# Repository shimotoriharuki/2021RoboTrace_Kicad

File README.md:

# 2021RoboTrace_Kicad

This repository contains circuit data for line-following robot ([UnderBird](https://www.youtube.com/watch?v=3UgktZoH9lk)).

Sourse code is [HERE](https://github.com/shimotoriharuki/2021RoboTracer).

Electronic components list is [HERE](https://lizard-building-630.notion.site/Electronic-components-list-d9b10301a8f747e9818a21101504a1fe).

# License: [GNU General Public License v3.0](https://github.com/shimotoriharuki/2021RoboTrace_Kicad/blob/master/COPYING)

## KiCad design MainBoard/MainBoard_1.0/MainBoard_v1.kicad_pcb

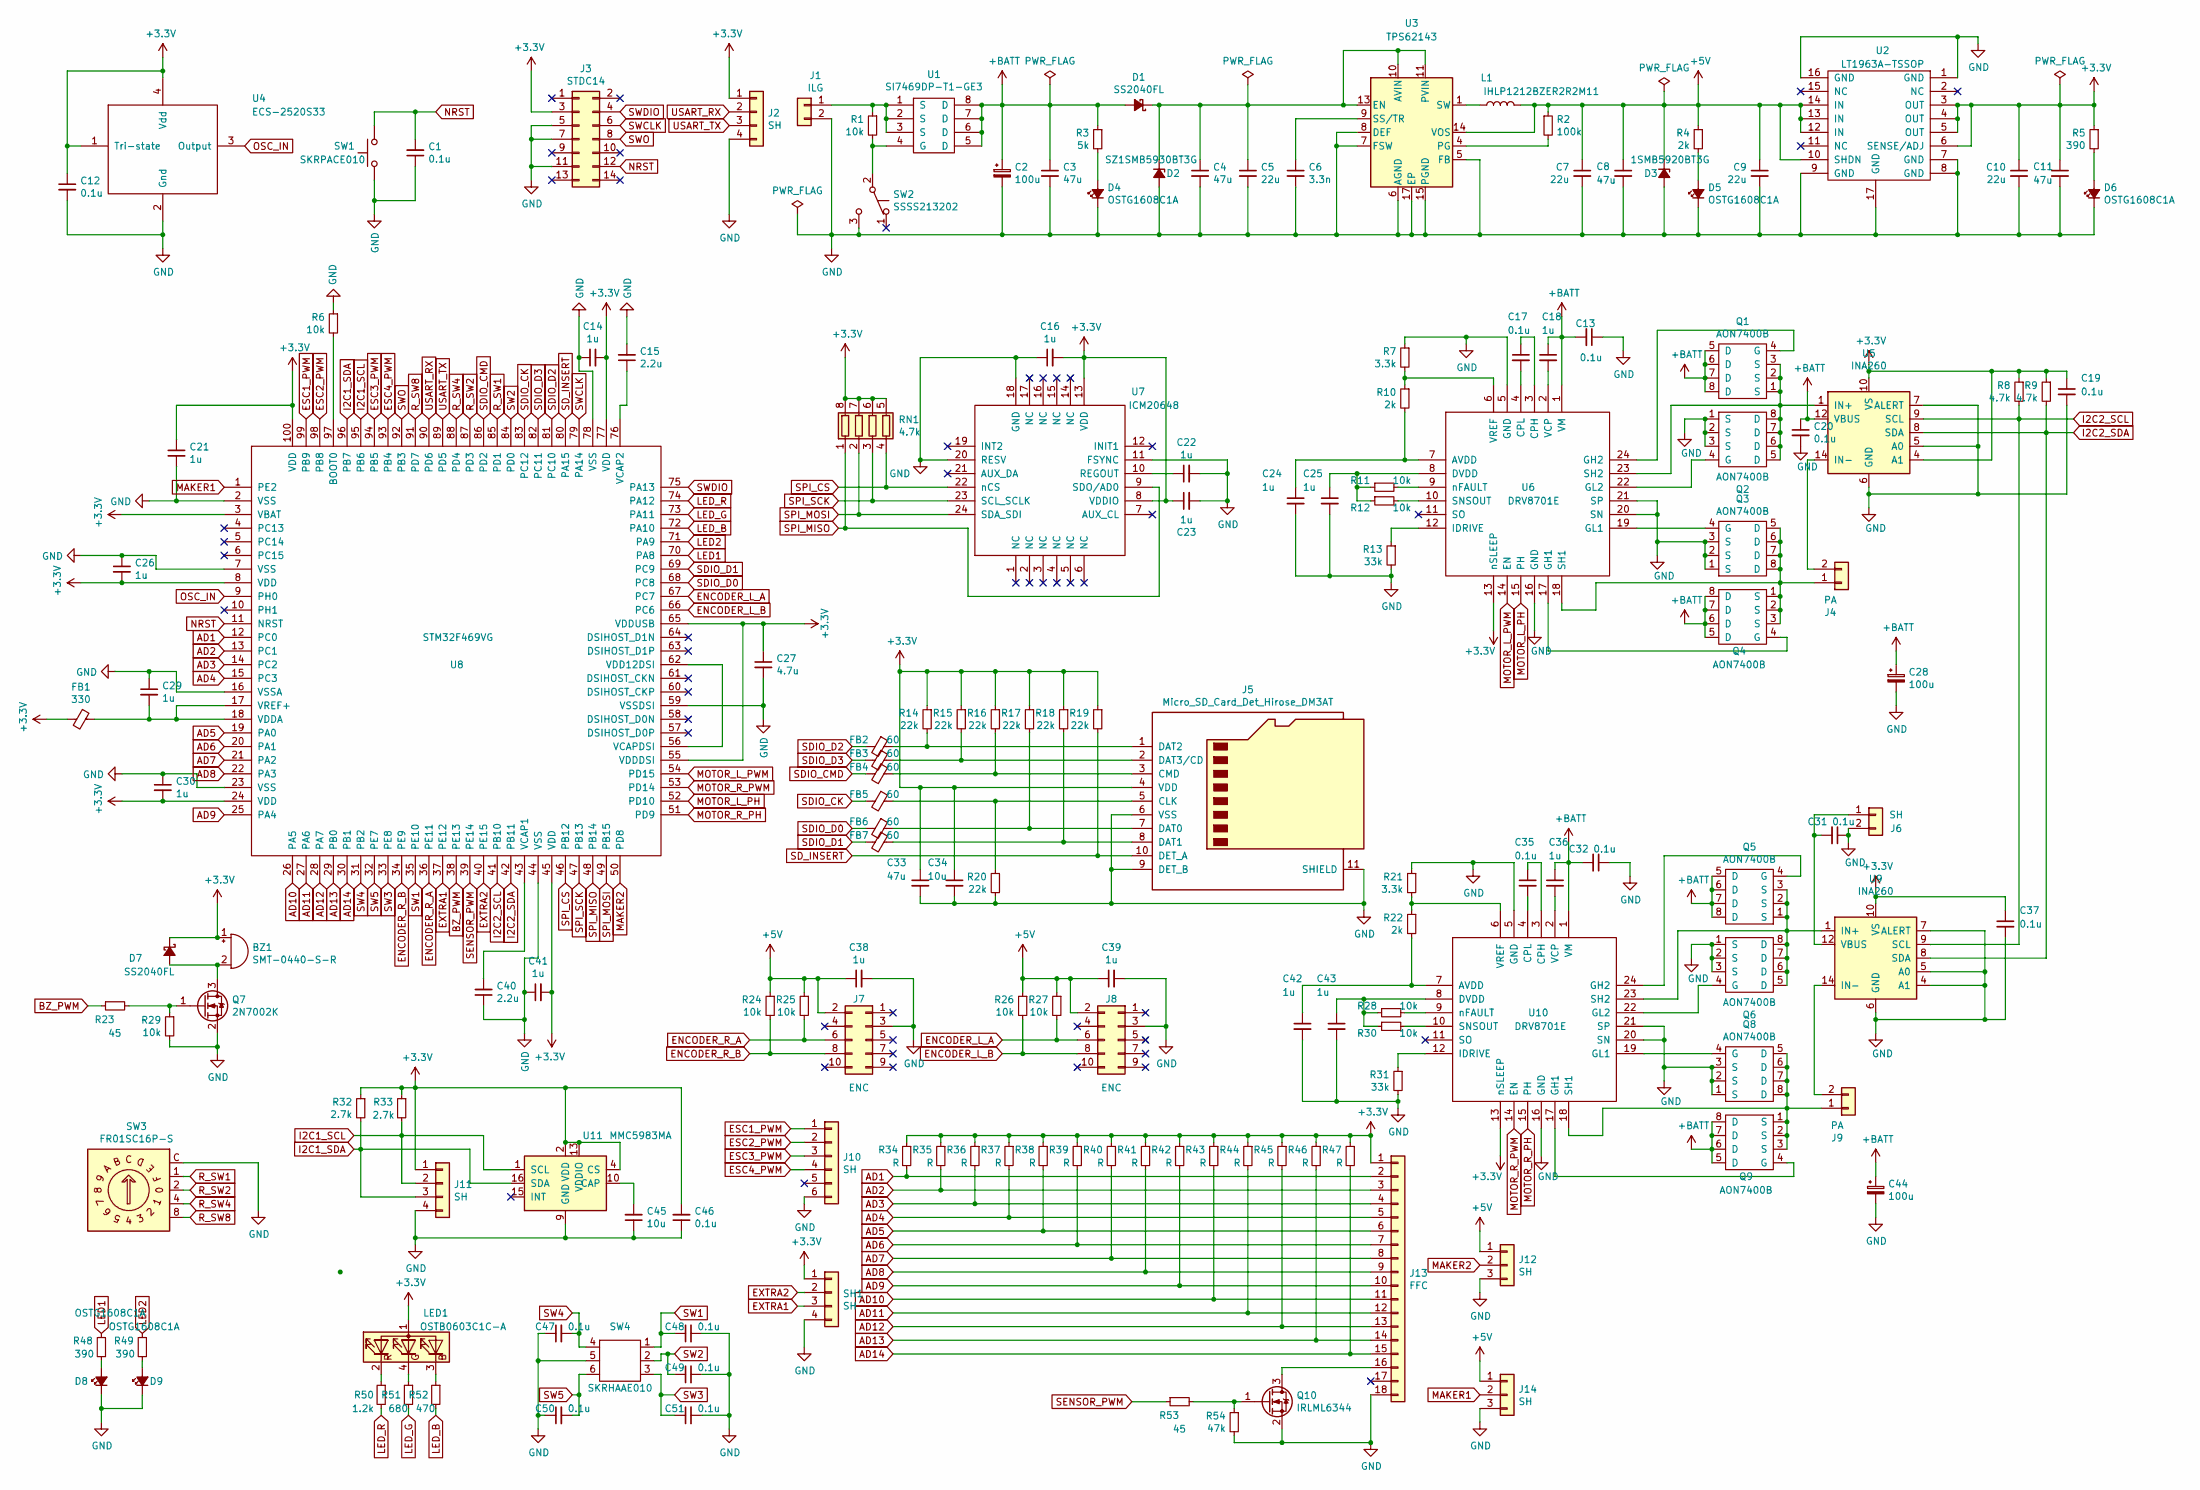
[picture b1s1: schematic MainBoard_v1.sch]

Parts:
BZ1: SMT-0440-S-R
C1, C12, C13, C17, C19, C20, C31, C32, C35, C37, C46, C47, C48, C49, C50, C51: 0.1u; C_0603
C2: 100u; CP_Elec_6.3x5.9
C3, C4, C8, C11, C33: 47u; C_1210
C5, C7, C9, C10: 22u; C_0805
C6: 3.3n; C_0603
C14, C16, C18, C21, C22, C23, C24, C25, C26, C29, C30, C36, C38, C39, C41, C42, C43: 1u; C_0603
C15, C40: 2.2u; C_0603
C27: 4.7u; C_0603
C28, C44: 100u; CP_Elec_5x5.8
C34, C45: 10u; C_0603
D1, D7: SS2040FL; D_SOD-123F
D2: SZ1SMB5930BT3G; 1SMB5930BT3G
D3: 1SMB5920BT3G; 1SMB5930BT3G
D4, D5, D6, D8, D9: OSTG1608C1A; LED_0603
FB1: 330; L_0603
FB2, FB3, FB4, FB5, FB6, FB7: 60; L_0603
J1: ILG; ILG_2pin
J2, J11: SH; JST_SH_BM04B-SRSS-TB_04x1.00mm_Straight
J3: STDC14; PinHeader_2x07_P1.27mm_Vertical_SMD
J4, J9: PA; PA_2pin
J5: Micro_SD_Card_Det_Hirose_DM3AT; Hirose_DM3AT-SF-PEJM5
J6: SH; JST_SH_BM02B-SRSS-TB_02x1.00mm_Straight
J7, J8: ENC; Pin_Header_Straight_2x05_Pitch1.27mm
J10: SH; JST_SH_BM06B-SRSS-TB_06x1.00mm_Straight
J12, J14: SH; JST_SH_BM03B-SRSS-TB_03x1.00mm_Straight
J13: FFC; Molex_FFC_18
L1: IHLP1212BZER2R2M11
LED1: OSTB0603C1C-A
Q1, Q2, Q3, Q4, Q5, Q6, Q8, Q9: AON7400B; DFN-8-1EP_3x3mm_P0.65mm_EP1.55x2.4mm
Q7: 2N7002K; SOT-23
Q10: IRLML6344; SOT-23
R1, R6, R11, R12, R24, R25, R26, R27, R28, R29, R30: 10k; R_0603
R2: 100k; R_0603
R3: 5k; R_0603
R4, R10, R22: 2k; R_0603
R5, R48, R49: 390; R_0603
R7, R21: 3.3k; R_0603
R8, R9: 4.7k; R_0603
R13, R31: 33k; R_0603
R14, R15, R16, R17, R18, R19, R20: 22k; R_0603
R23, R53: 45; R_0603
R32, R33: 2.7k; R_0603
R34, R35, R36, R37, R38, R39, R40, R41, R42, R43, R44, R45, R46, R47: R; R_0603
R50: 1.2k; R_0603
R51: 680; R_0603
R52: 470; R_0603
R54: 47k; R_0603
RN1: 4.7k; R_Array_Convex_4x1206
SH1: SH; JST_SH_BM04B-SRSS-TB_04x1.00mm_Straight
SW1: SKRPACE010
SW2: SSSS213202
SW3: FR01SC16P-S; FR01SC16P
SW4: SKRHAAE010
U1: SI7469DP-T1-GE3; SO-8_PowerPAK_Vishay_Single
U2: LT1963A-TSSOP; TSSOP-16-1EP_4.4x5mm_Pitch0.65mm
U3: TPS62143; TPS62143RGTR
U4: ECS-2520S33; Crystal_SMD_2520-4pin_2.5x2.0mm
U5, U9: INA260; TSSOP-16_4.4x5mm_Pitch0.65mm
U6, U10: DRV8701E; DRV8701ERGET
U7: ICM20648
U8: STM32F469VG; LQFP-100_14x14mm_Pitch0.5mm
U11: MMC5983MA

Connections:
+3V3: BZ1.1 (-), C10.1, C11.1, C12.1, C14.2, C16.2, C19.1, C21.1, C23.1, C26.2, C27.1, C30.2, C33.1, C34.1, C37.1, C41.2, C46.2, D7.1 (K), FB1.2, J2.1, J3.3, J5.4 (VDD), J11.1, J13.1, LED1.1, R5.1, R8.1, R9.1, R14.1, R15.1, R16.1, R17.1, R18.1, R19.1, R32.1, R33.1, R34.1, R35.1, R36.1, R37.1, R38.1, R39.1, R40.1, R41.1, R42.1, R43.1, R44.1, R45.1, R46.1, R47.1, RN1.5 (R4.2), RN1.6 (R3.2), RN1.7 (R2.2), RN1.8 (R1.2), SH1.1, U2.3 (OUT), U2.4 (OUT), U2.5 (OUT), U2.6 (SENSE/ADJ), U4.1 (Tri-state), U4.4 (Vdd), U5.4 (A1), U5.10 (VS), U6.13 (nSLEEP), U7.8 (VDDIO), U7.13 (VDD), U8.3 (VBAT), U8.8 (VDD), U8.24 (VDD), U8.45 (VDD), U8.55 (VDDDSI), U8.65 (VDDUSB), U8.77 (VDD), U8.100 (VDD), U9.10 (VS), U10.13 (nSLEEP), U11.2 (VDD), U11.4 (CS), U11.13 (VDDIO)
+5V: C7.1, C8.1, C9.1, C38.1, C39.1, D3.1 (K), J7.2, J8.2, J12.1, J14.1, L1.2, R2.1, R4.1, R24.1, R25.1, R26.1, R27.1, U2.10 (SHDN), U2.12 (IN), U2.13 (IN), U2.14 (IN), U3.14 (VOS)
+BATT: C2.1, C3.1, C13.2, C18.1, C20.1, C28.1, C32.2, C36.1, C44.1, D1.2 (A), Q1.5 (D), Q1.6 (D), Q1.7 (D), Q1.8 (D), Q4.5 (D), Q4.6 (D), Q4.7 (D), Q4.8 (D), Q5.5 (D), Q5.6 (D), Q5.7 (D), Q5.8 (D), Q9.5 (D), Q9.6 (D), Q9.7 (D), Q9.8 (D), R3.1, U1.5 (D), U1.6 (D), U1.7 (D), U1.8 (D), U5.12 (VBUS), U6.1 (VM), U10.1 (VM)
AD1: J13.2, R34.2, U8.12 (PC0)
AD2: J13.3, R35.2, U8.13 (PC1)
AD3: J13.4, R36.2, U8.14 (PC2)
AD4: J13.5, R37.2, U8.15 (PC3)
AD5: J13.6, R38.2, U8.19 (PA0)
AD6: J13.7, R39.2, U8.20 (PA1)
AD7: J13.8, R40.2, U8.21 (PA2)
AD8: J13.9, R41.2, U8.22 (PA3)
AD9: J13.10, R42.2, U8.25 (PA4)
AD10: J13.11, R43.2, U8.26 (PA5)
AD11: J13.12, R44.2, U8.27 (PA6)
AD12: J13.13, R45.2, U8.28 (PA7)
AD13: J13.14, R46.2, U8.29 (PB0)
AD14: J13.15, R47.2, U8.30 (PB1)
BZ_PWM: R23.1, U8.38 (PE13)
ENCODER_L_A: J8.6, R27.2, U8.67 (PC7)
ENCODER_L_B: J8.8, R26.2, U8.66 (PC6)
ENCODER_R_A: J7.6, R25.2, U8.36 (PE11)
ENCODER_R_B: J7.8, R24.2, U8.34 (PE9)
ESC1_PWM: J10.1, U8.99 (PB9)
ESC2_PWM: J10.2, U8.98 (PB8)
ESC3_PWM: J10.3, U8.94 (PB5)
ESC4_PWM: J10.4, U8.93 (PB4)
EXTRA1: SH1.3, U8.37 (PE12)
EXTRA2: SH1.2, U8.40 (PE15)
GND: C1.1, C2.2, C3.2, C4.2, C5.2, C6.2, C7.2, C8.2, C9.2, C10.2, C11.2, C12.2, C13.1, C14.1, C15.2, C16.1, C19.2, C20.2, C21.2, C22.2, C23.2, C24.2, C25.2, C26.1, C27.2, C28.2, C29.1, C30.1, C31.1, C32.1, C33.2, C34.2, C37.2, C38.2, C39.2, C40.1, C41.1, C42.2, C43.2, C44.2, C45.1, C46.1, C47.1, C48.2, C49.2, C50.1, C51.2, D2.2 (A), D3.2 (A), D4.1 (K), D5.1 (K), D6.1 (K), D8.1 (K), D9.1 (K), J1.2, J2.4, J3.5, J3.7, J3.11, J5.6 (VSS), J5.9 (DET_B), J5.11 (SHIELD), J6.2, J7.3, J8.3, J10.6, J11.4, J12.3, J13.18, J14.3, Q2.1 (S), Q2.2 (S), Q2.3 (S), Q3.1 (S), Q3.2 (S), Q3.3 (S), Q6.1 (S), Q6.2 (S), Q6.3 (S), Q7.2 (S), Q8.1 (S), Q8.2 (S), Q8.3 (S), Q10.2 (S), R6.1, R7.1, R13.2, R20.2, R21.1, R29.2, R31.2, R54.2, SH1.4, SW1.2, SW2.3 (C), SW3.C, SW4.5, U2.1 (GND), U2.7 (GND), U2.8 (GND), U2.9 (GND), U2.16 (GND), U2.17 (GND), U3.5 (FB), U3.6 (AGND), U3.7 (FSW), U3.8 (DEF), U3.15 (PGND), U3.16 (PGND), U3.17 (EP), U4.2 (Gnd), U5.5 (A0), U5.6 (GND), U5.7 (ALERT), U5.11 (GND), U6.5 (GND), U6.16 (GND), U6.20 (SN), U6.21 (SP), U7.11 (FSYNC), U7.18 (GND), U7.20 (RESV), U8.2 (VSS), U8.7 (VSS), U8.16 (VSSA), U8.23 (VSS), U8.44 (VSS), U8.59 (VSSDSI), U8.78 (VSS), U9.4 (A1), U9.5 (A0), U9.6 (GND), U9.7 (ALERT), U9.11 (GND), U10.5 (GND), U10.16 (GND), U10.20 (SN), U10.21 (SP), U11.9 (GND), U11.11 (GND)
I2C1_SCL: J11.2, R33.2, U8.95 (PB6), U11.1 (SCL)
I2C1_SDA: J11.3, R32.2, U8.96 (PB7), U11.16 (SDA)
I2C2_SCL: R8.2, U5.9 (SCL), U8.41 (PB10), U9.9 (SCL)
I2C2_SDA: R9.2, U5.8 (SDA), U8.42 (PB11), U9.8 (SDA)
LED1: R48.1, U8.70 (PA8)
LED2: R49.1, U8.71 (PA9)
LED_B: R52.2, U8.72 (PA10)
LED_G: R51.2, U8.73 (PA11)
LED_R: R50.2, U8.74 (PA12)
MAKER1: J14.2, U8.1 (PE2)
MAKER2: J12.2, U8.50 (PD8)
MOTOR_L_PH: U6.15 (PH), U8.52 (PD10)
MOTOR_L_PWM: U6.14 (EN), U8.54 (PD15)
MOTOR_R_PH: U8.51 (PD9), U10.15 (PH)
MOTOR_R_PWM: U8.53 (PD14), U10.14 (EN)
NRST: C1.2, J3.12, SW1.1, U8.11 (NRST)
unnamed: BZ1.2 (+), D7.2 (A), Q7.3 (D)
unnamed: C4.1, C5.1, D1.1 (K), D2.1 (K), U3.10 (AVIN), U3.11 (PVIN), U3.12 (PVIN), U3.13 (EN)
unnamed: C6.1, U3.9 (SS/TR)
unnamed: C15.1, U8.76 (VCAP2)
unnamed: C17.1, U6.3 (CPH)
unnamed: C17.2, U6.4 (CPL)
unnamed: C18.2, U6.2 (VCP)
unnamed: C22.1, U7.10 (REGOUT)
unnamed: C24.1, R10.2, U6.7 (AVDD)
unnamed: C25.1, R11.1, R12.1, U6.8 (DVDD)
unnamed: C29.2, FB1.1, U8.17 (VREF+), U8.18 (VDDA)
unnamed: C31.2, J6.1, U9.12 (VBUS)
unnamed: C35.1, U10.3 (CPH)
unnamed: C35.2, U10.4 (CPL)
unnamed: C36.2, U10.2 (VCP)
unnamed: C40.2, U8.43 (VCAP1)
unnamed: C42.1, R22.2, U10.7 (AVDD)
unnamed: C43.1, R28.1, R30.1, U10.8 (DVDD)
unnamed: C45.2, U11.10 (CAP)
unnamed: D4.2 (A), R3.2
unnamed: D5.2 (A), R4.2
unnamed: D6.2 (A), R5.2
unnamed: D8.2 (A), R48.2
unnamed: D9.2 (A), R49.2
unnamed: FB2.1, J5.1 (DAT2), R14.2
unnamed: FB3.1, J5.2 (DAT3/CD), R15.2
unnamed: FB4.1, J5.3 (CMD), R16.2
unnamed: FB5.1, J5.5 (CLK), R20.1
unnamed: FB6.1, J5.7 (DAT0), R17.2
unnamed: FB7.1, J5.8 (DAT1), R18.2
unnamed: J1.1, R1.1, U1.1 (S), U1.2 (S), U1.3 (S)
unnamed: J4.1, Q3.5 (D), Q3.6 (D), Q3.7 (D), Q3.8 (D), Q4.1 (S), Q4.2 (S), Q4.3 (S), U6.18 (SH1)
unnamed: J4.2, U5.14 (IN-), U5.15 (IN-), U5.16 (IN-)
unnamed: J9.1, Q8.5 (D), Q8.6 (D), Q8.7 (D), Q8.8 (D), Q9.1 (S), Q9.2 (S), Q9.3 (S), U10.18 (SH1)
unnamed: J9.2, U9.14 (IN-), U9.15 (IN-), U9.16 (IN-)
unnamed: J13.16, Q10.3 (D)
unnamed: L1.1, U3.1 (SW), U3.2 (SW), U3.3 (SW)
unnamed: LED1.2, R50.1
unnamed: LED1.3, R52.1
unnamed: LED1.4, R51.1
unnamed: Q1.1 (S), Q1.2 (S), Q1.3 (S), Q2.5 (D), Q2.6 (D), Q2.7 (D), Q2.8 (D), U5.1 (IN+), U5.2 (IN+), U5.3 (IN+), U6.23 (SH2)
unnamed: Q1.4 (G), U6.24 (GH2)
unnamed: Q2.4 (G), U6.22 (GL2)
unnamed: Q3.4 (G), U6.19 (GL1)
unnamed: Q4.4 (G), U6.17 (GH1)
unnamed: Q5.1 (S), Q5.2 (S), Q5.3 (S), Q6.5 (D), Q6.6 (D), Q6.7 (D), Q6.8 (D), U9.1 (IN+), U9.2 (IN+), U9.3 (IN+), U10.23 (SH2)
unnamed: Q5.4 (G), U10.24 (GH2)
unnamed: Q6.4 (G), U10.22 (GL2)
unnamed: Q7.1 (G), R23.2, R29.1
unnamed: Q8.4 (G), U10.19 (GL1)
unnamed: Q9.4 (G), U10.17 (GH1)
unnamed: Q10.1 (G), R53.2, R54.1
unnamed: R1.2, SW2.2 (B), U1.4 (G)
unnamed: R2.2, U3.4 (PG)
unnamed: R6.2, U8.97 (BOOT0)
unnamed: R7.2, R10.1, U6.6 (VREF)
unnamed: R11.2, U6.9 (nFAULT)
unnamed: R12.2, U6.10 (SNSOUT)
unnamed: R13.1, U6.12 (IDRIVE)
unnamed: R21.2, R22.1, U10.6 (VREF)
unnamed: R28.2, U10.9 (nFAULT)
unnamed: R30.2, U10.10 (SNSOUT)
unnamed: R31.1, U10.12 (IDRIVE)
unnamed: U8.56 (VCAPDSI), U8.62 (VDD12DSI)
OSC_IN: U4.3 (Output), U8.9 (PH0)
R_SW1: SW3.1, U8.85 (PD1)
R_SW2: SW3.2, U8.87 (PD3)
R_SW4: SW3.4, U8.88 (PD4)
R_SW8: SW3.8, U8.91 (PD7)
SDIO_CK: FB5.2, U8.83 (PC12)
SDIO_CMD: FB4.2, U8.86 (PD2)
SDIO_D0: FB6.2, U8.68 (PC8)
SDIO_D1: FB7.2, U8.69 (PC9)
SDIO_D2: FB2.2, U8.81 (PC10)
SDIO_D3: FB3.2, U8.82 (PC11)
SD_INSERT: J5.10 (DET_A), R19.2, U8.80 (PA15)
SENSOR_PWM: R53.1, U8.39 (PE14)
SPI_CS: RN1.4 (R4.1), U7.22 (nCS), U8.46 (PB12)
SPI_MISO: RN1.1 (R1.1), U7.9 (SDO/AD0), U8.48 (PB14)
SPI_MOSI: RN1.2 (R2.1), U7.24 (SDA_SDI), U8.49 (PB15)
SPI_SCK: RN1.3 (R3.1), U7.23 (SCL_SCLK), U8.47 (PB13)
SW1: C48.1, SW4.1, U8.35 (PE10)
SW2: C49.1, SW4.2, U8.84 (PD0)
SW3: C51.1, SW4.3, U8.33 (PE8)
SW4: C47.2, SW4.4, U8.31 (PB2)
SW5: C50.2, SW4.6, U8.32 (PE7)
SWCLK: J3.6, U8.79 (PA14)
SWDIO: J3.4, U8.75 (PA13)
SWO: J3.8, U8.92 (PB3)
USART_RX: J2.2, U8.90 (PD6)
USART_TX: J2.3, U8.89 (PD5)

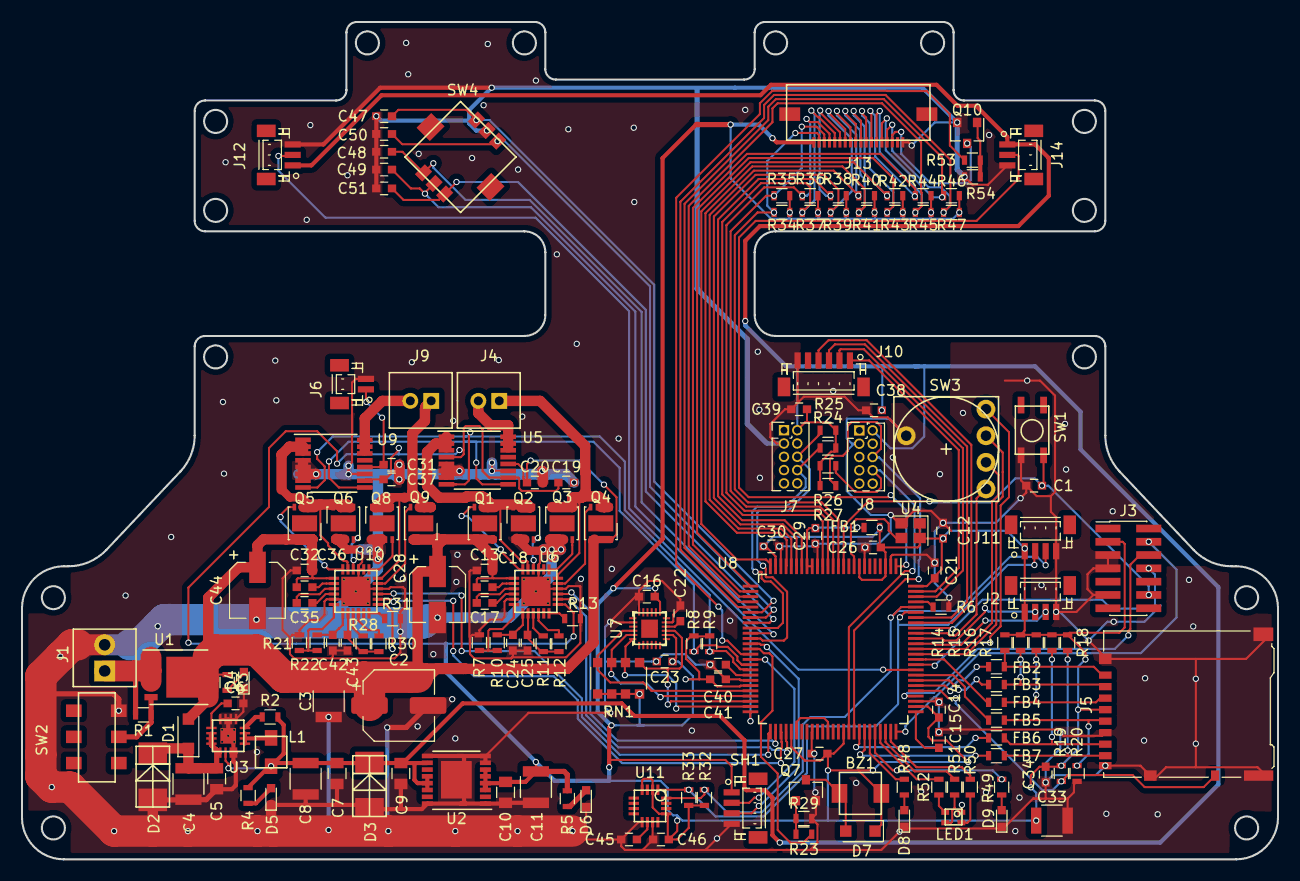
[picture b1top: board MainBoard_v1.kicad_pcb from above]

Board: 2 copper layers, 120.0 x 80.0 mm, 165 parts (0 on the bottom side), 136 nets.

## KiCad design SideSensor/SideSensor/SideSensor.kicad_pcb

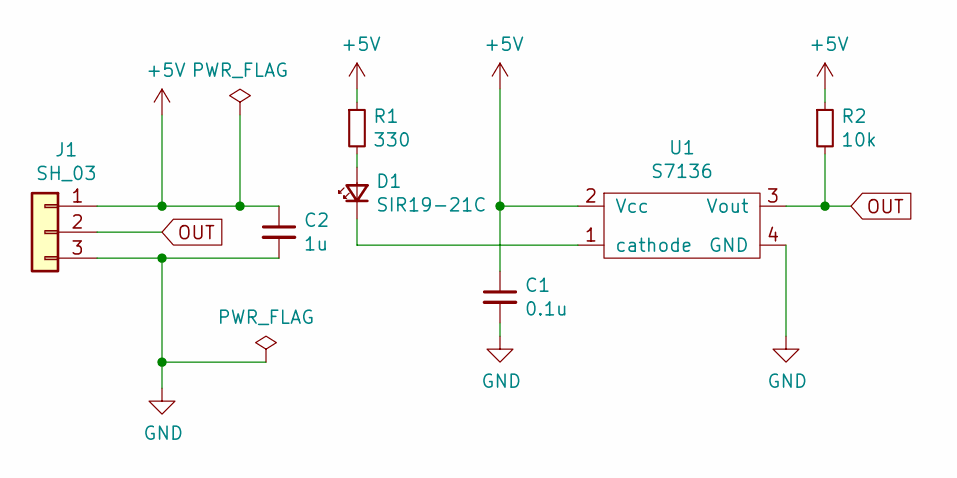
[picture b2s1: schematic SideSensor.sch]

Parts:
C1: 0.1u; C_0603_1608Metric
C2: 1u
D1: SIR19-21C
J1: SH_03; JST_SH_BM03B-SRSS-TB_1x03-1MP_P1.00mm_Vertical
R1: 330; R_0603_1608Metric
R2: 10k; R_0603_1608Metric
U1: S7136

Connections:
+5V: C1.1, C2.1, J1.1, R1.1, R2.1, U1.2 (Vcc)
GND: C1.2, C2.2, J1.3, U1.4 (GND)
unnamed: D1.1 (K), U1.1 (cathode)
unnamed: D1.2 (A), R1.2
OUT: J1.2, R2.2, U1.3 (Vout)

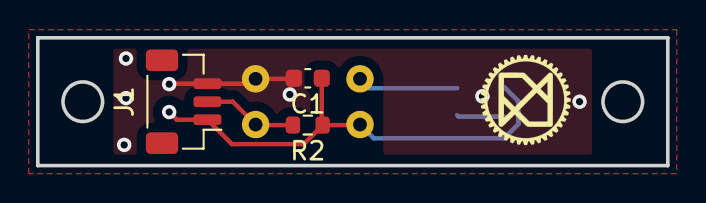
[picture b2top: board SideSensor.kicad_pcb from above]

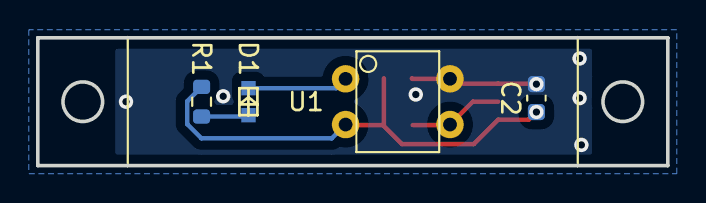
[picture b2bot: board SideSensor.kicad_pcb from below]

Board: 2 copper layers, 35.0 x 7.1 mm, 7 parts (4 on the bottom side), 5 nets.

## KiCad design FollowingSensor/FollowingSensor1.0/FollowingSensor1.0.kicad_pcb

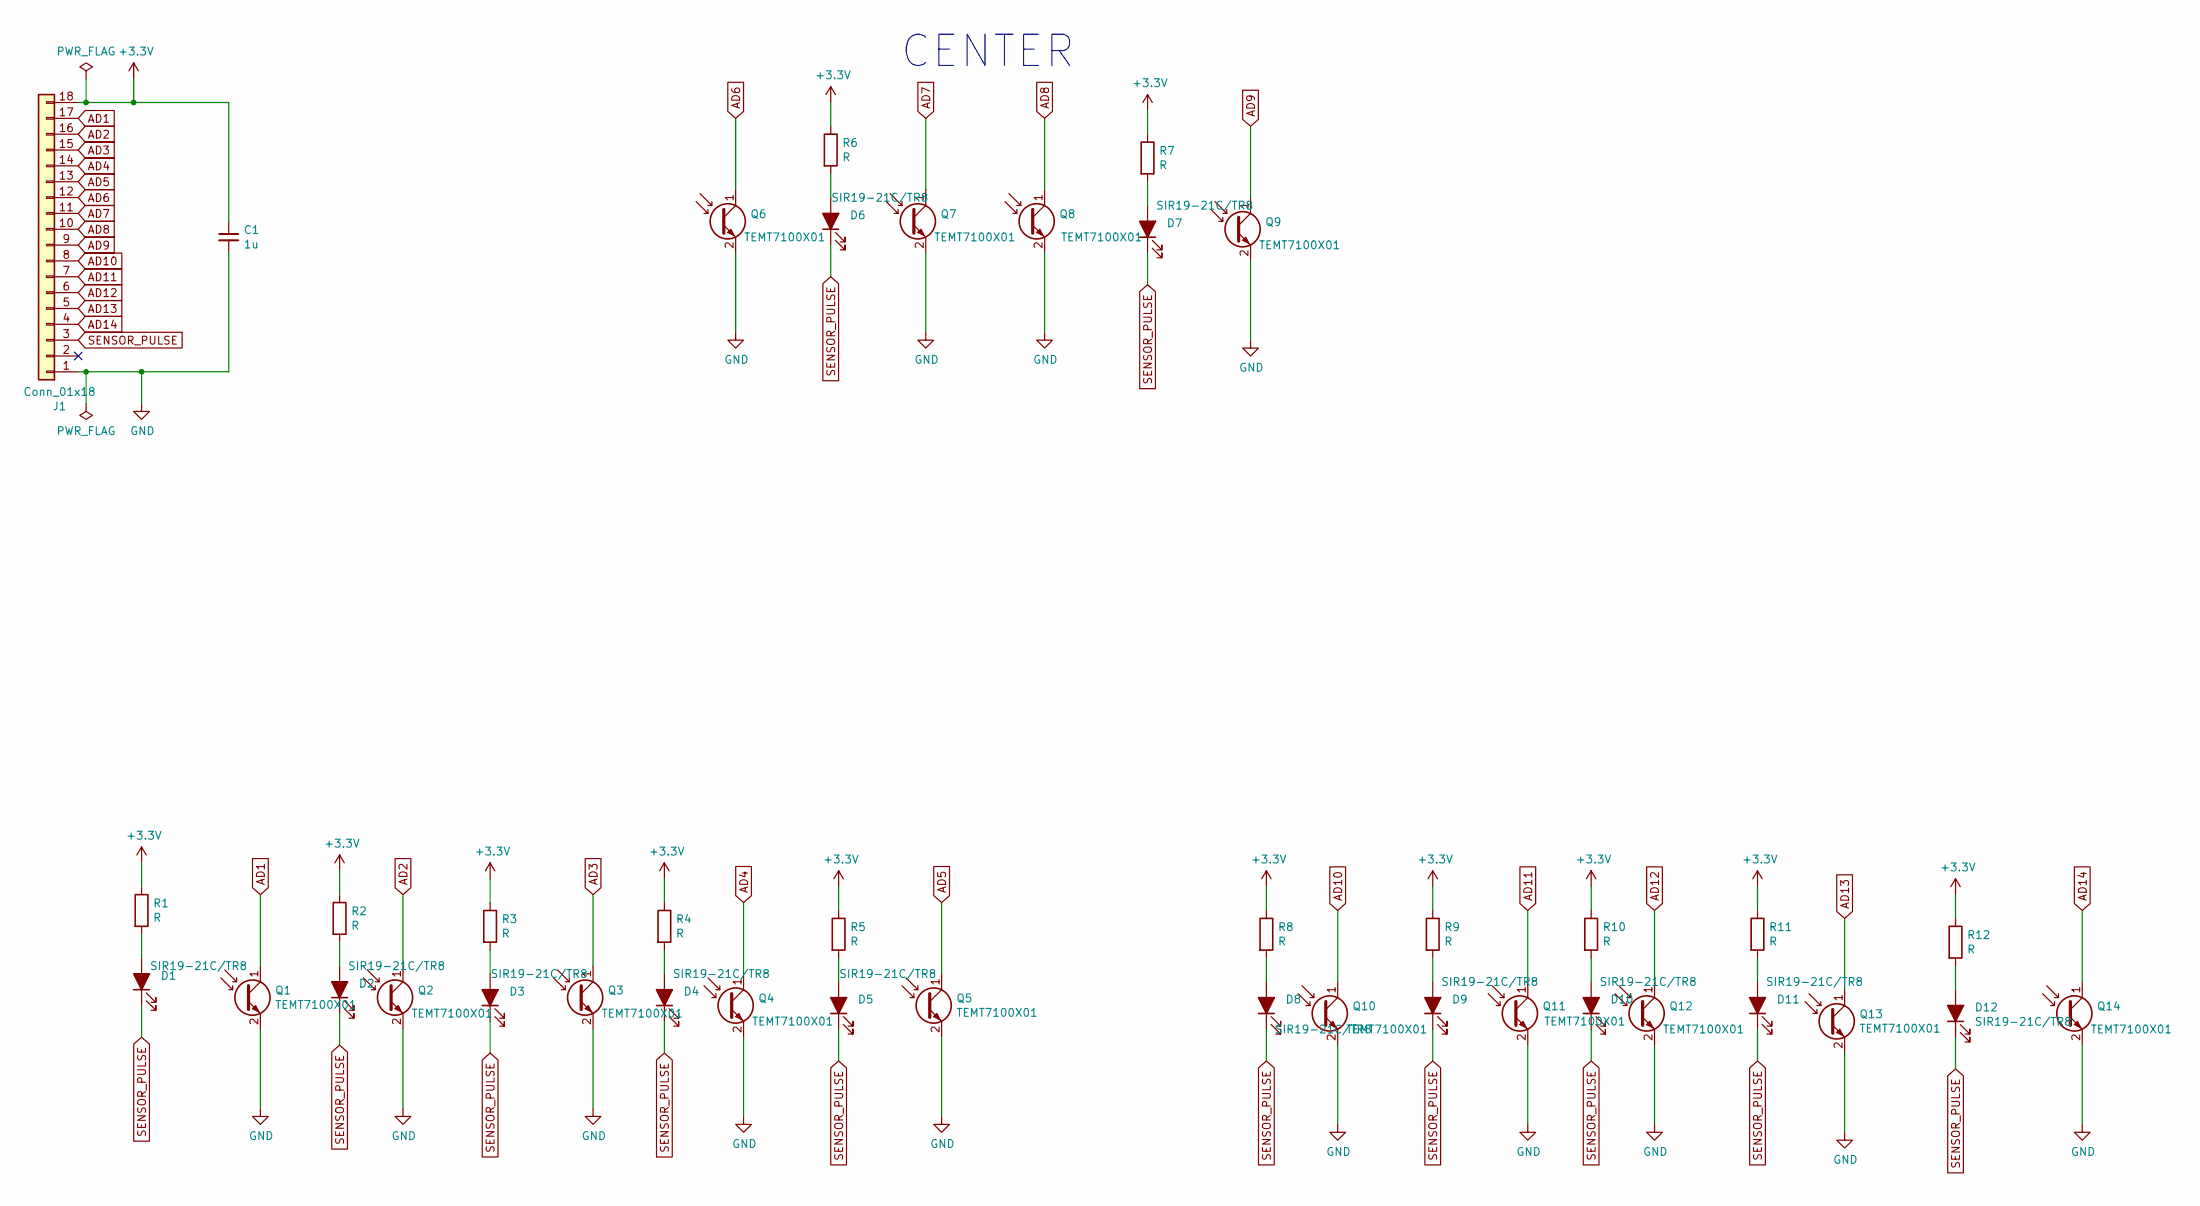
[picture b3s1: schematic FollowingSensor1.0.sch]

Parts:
C1: 1u; C_0603_1608Metric
D1, D2, D3, D4, D5, D6, D7, D8, D9, D10, D11, D12: SIR19-21C/TR8; SIR19-21C
J1: Conn_01x18; Molex_FFC_18
Q1, Q2, Q3, Q4, Q5, Q6, Q7, Q8, Q9, Q10, Q11, Q12, Q13, Q14: TEMT7100X01
R1, R2, R3, R4, R5, R6, R7, R8, R9, R10, R11, R12: R; R_0603_1608Metric

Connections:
+3V3: C1.1, J1.18, R1.1, R2.1, R3.1, R4.1, R5.1, R6.1, R7.1, R8.1, R9.1, R10.1, R11.1, R12.1
AD1: J1.17, Q1.1 (C)
AD2: J1.16, Q2.1 (C)
AD3: J1.15, Q3.1 (C)
AD4: J1.14, Q4.1 (C)
AD5: J1.13, Q5.1 (C)
AD6: J1.12, Q6.1 (C)
AD7: J1.11, Q7.1 (C)
AD8: J1.10, Q8.1 (C)
AD9: J1.9, Q9.1 (C)
AD10: J1.8, Q10.1 (C)
AD11: J1.7, Q11.1 (C)
AD12: J1.6, Q12.1 (C)
AD13: J1.5, Q13.1 (C)
AD14: J1.4, Q14.1 (C)
GND: C1.2, J1.1, Q1.2 (E), Q2.2 (E), Q3.2 (E), Q4.2 (E), Q5.2 (E), Q6.2 (E), Q7.2 (E), Q8.2 (E), Q9.2 (E), Q10.2 (E), Q11.2 (E), Q12.2 (E), Q13.2 (E), Q14.2 (E)
unnamed: D1.2 (A), R1.2
unnamed: D2.2 (A), R2.2
unnamed: D3.2 (A), R3.2
unnamed: D4.2 (A), R4.2
unnamed: D5.2 (A), R5.2
unnamed: D6.2 (A), R6.2
unnamed: D7.2 (A), R7.2
unnamed: D8.2 (A), R8.2
unnamed: D9.2 (A), R9.2
unnamed: D10.2 (A), R10.2
unnamed: D11.2 (A), R11.2
unnamed: D12.2 (A), R12.2
SENSOR_PULSE: D1.1 (K), D2.1 (K), D3.1 (K), D4.1 (K), D5.1 (K), D6.1 (K), D7.1 (K), D8.1 (K), D9.1 (K), D10.1 (K), D11.1 (K), D12.1 (K), J1.3

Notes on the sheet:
CENTER

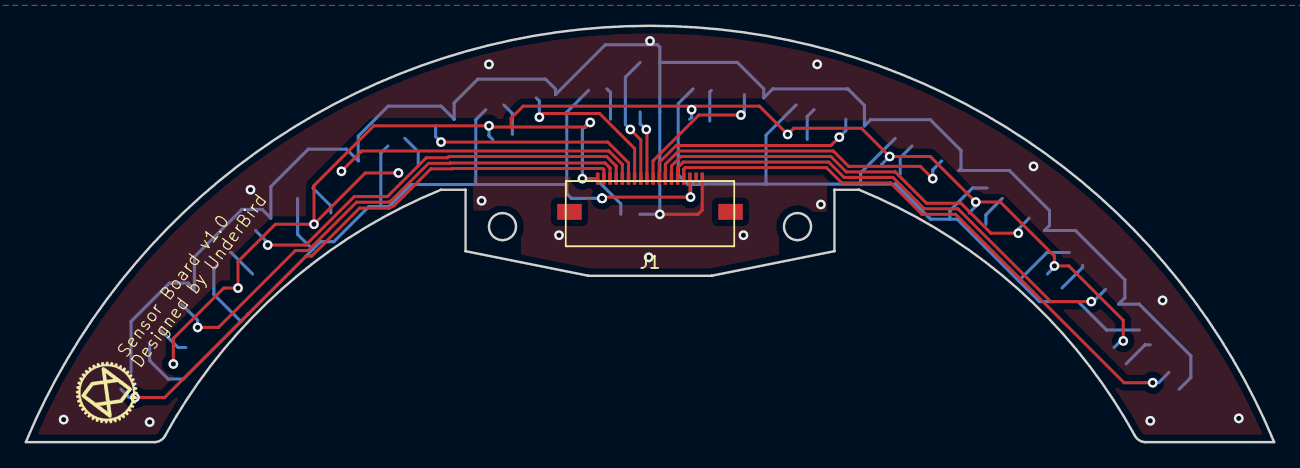
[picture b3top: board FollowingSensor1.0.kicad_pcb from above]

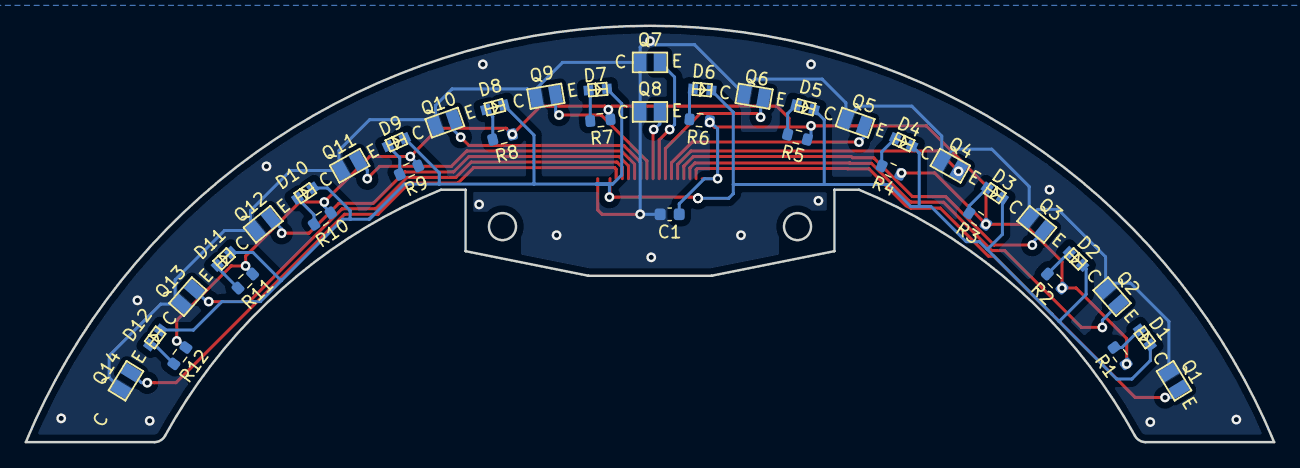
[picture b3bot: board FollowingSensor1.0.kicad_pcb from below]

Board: 2 copper layers, 101.6 x 33.9 mm, 40 parts (39 on the bottom side), 29 nets.

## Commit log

2020-06-14 init
2020-07-06 もう少しで完成
2021-05-05 ver_2021
2021-05-08 update edge
2021-05-08 fixed up_right
2021-05-09 fixed right bottom
2021-05-10 fixed up right
2021-05-10 wiring completed
2021-05-10 LinesensorUpdate
2021-05-10 sensor on the way
2021-05-11 placement phototransister
2021-05-11 following sensor designed
2021-05-11 fixed main_board
2021-05-11 fixed sensor_board
2021-05-11 add side sensor
2021-05-11 add logo
2021-05-12 remove antena and move referencse by main board
2021-05-12 moved reference
2021-05-12 moved silks
2021-05-12 complete
2021-05-12 before confirmation
2021-05-12 change capaciter size
2021-05-12 fixed
2021-05-12 export gerber
2021-05-13 change FET footprint
2021-06-06 センサの抵抗値などを変更
2021-06-08 再プッシュ
2022-03-30 Create COPYING
2022-09-22 ファイル構成変更と回路図のpdf追加
